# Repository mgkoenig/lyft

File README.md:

# LYFT
LYFT is a sophisticated remote control for the famous IKEA BEKANT desk. It replaces the original controller and adds a number of useful features for more options and convenience. 

Check [tindie](https://www.tindie.com/products/mgkoenig/lyft/) to see a fully assembled version of LYFT in action. 

If you would like to read a featured article about LYFT you can find some on [ikeahackers](https://ikeahackers.net/2024/03/ikea-adjustable-desk.html) or [hackaday](https://hackaday.com/2024/04/18/lyft-standing-up-for-better-ikea-bekant-control/) respectively. 

## Features 
#### Saving Desk Positions  
The controller can store up to four different desk positions. These positions are easily accessable using the four memory buttons.

#### Display 
The controller is equipped with a 3-digit 7-segment display which allows you to read the current desk height either in centimeters or inch. Furthermore, you can adjust the display brigtness as well as the display-on time. If the shown desk height is not accurate you can adjust the value using the 'level correction' feature by plus/minus 9 centimeters. 
  
#### Audio Signals  
In order to give some acoustic feedback the controller has a build-in audio transducer. The volume of the audio signals can be set in the settings menu but also be disabled.
  
#### Automatic Driving Mode
One of the most useful features is the automatic driving mode which allows you to move the desk to a saved position without holding a button all the time. 

#### Safety Pin 
On the basis of the original controller LYFT also supports a safety pin. The pin is needed to move the desk and to unlock the settings menu for changes. It is fully compatible with the original IKEA safety pin which is provided with the BEKANT desk. 

Further details and how to use these features are described in the [manual](/manual.pdf).

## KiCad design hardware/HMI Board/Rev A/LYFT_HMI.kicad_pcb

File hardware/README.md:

# LYFT Hardware 
The LYFT hardware consists of two PCB boards. A controller board and an HMI board. 

### Controller Board
The controller board holds the SAM-D21 micrcontroller and handles all the motor control as well as the HMI communication. Desk motors are addressed using the LIN bus while the HMI board is connected via I2C. A buzzer is used to generate sounds and alarms. 

### HMI Board
The HMI board is equipped with an AS1115 display driver to control both the 7-segment display and all six buttons. 

### Library
Parts which are not existent in the standard KiCad library are published here.

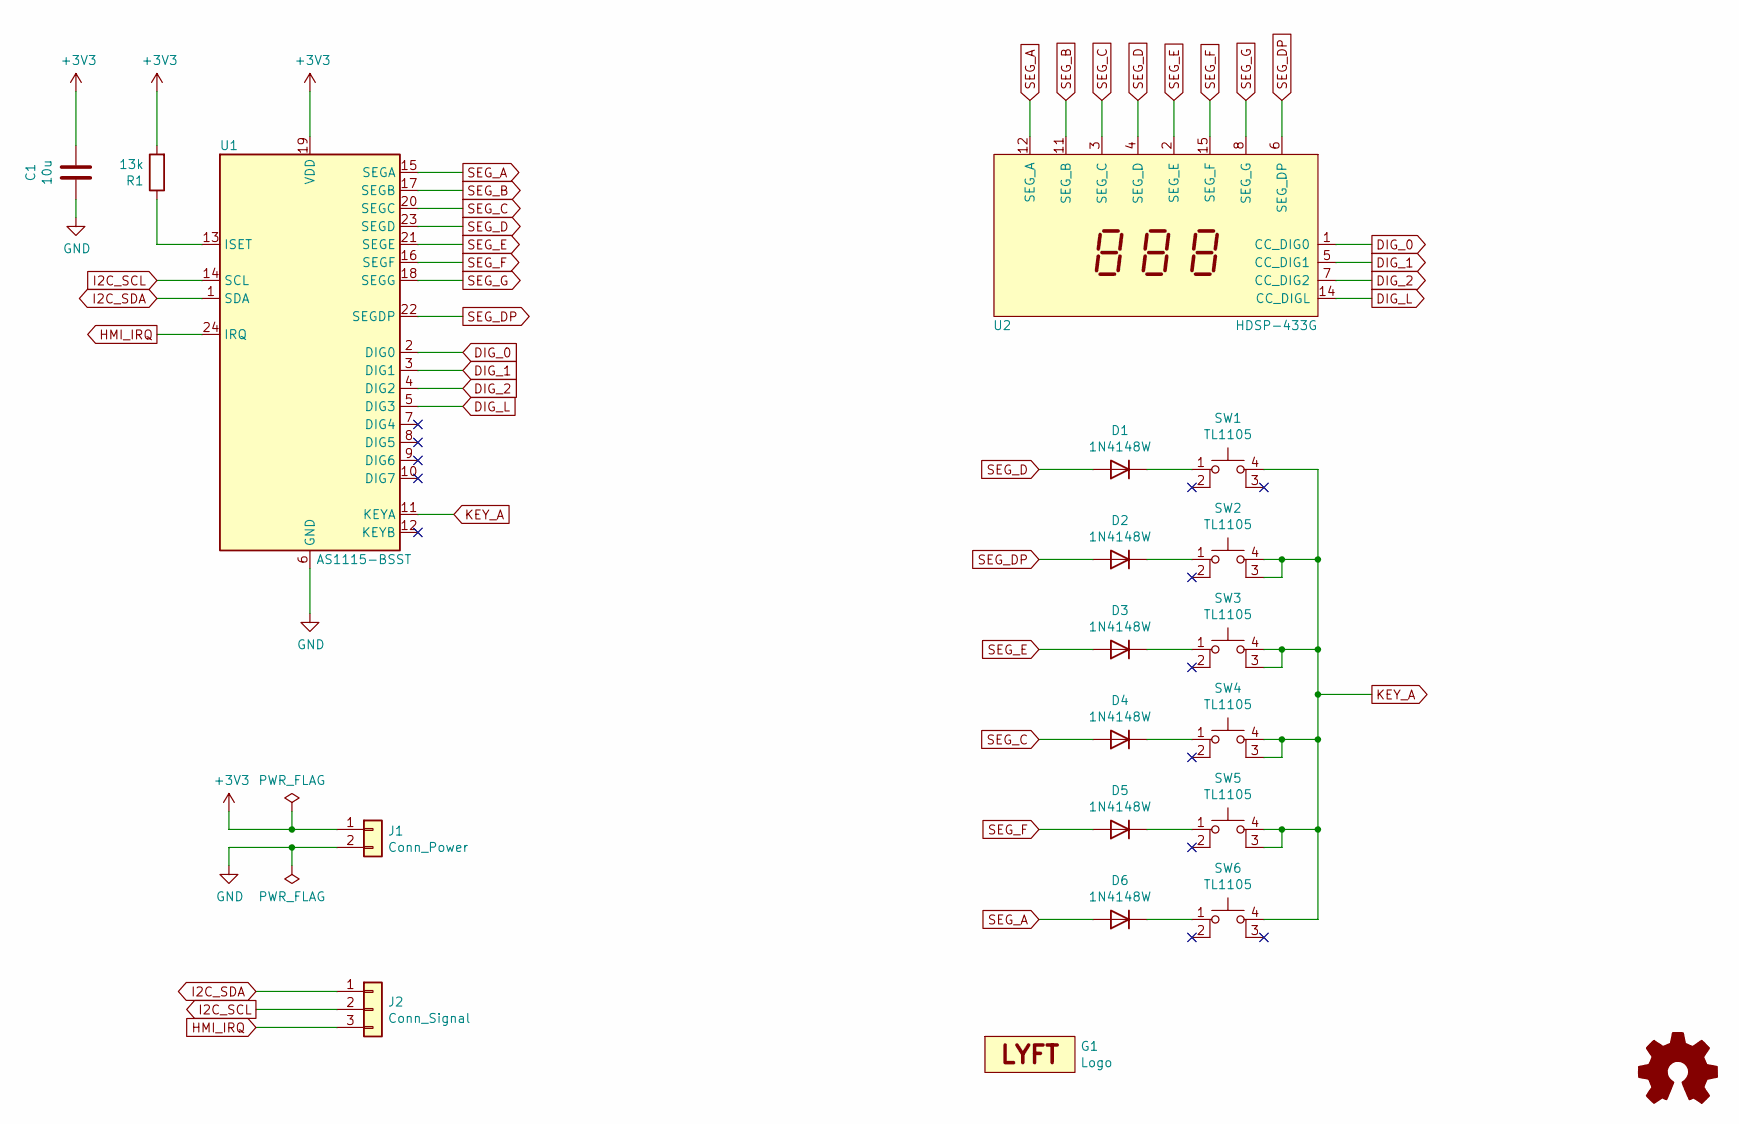
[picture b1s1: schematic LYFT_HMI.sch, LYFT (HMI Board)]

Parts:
C1: 10u; C_0805_2012Metric_Pad1.18x1.45mm_HandSolder
D1, D2, D3, D4, D5, D6: 1N4148W; D_SOD-123
G1: Logo; LYFT-Logo_10x4
J1: Conn_Power; PinSocket_1x02_P2.54mm_Vertical
J2: Conn_Signal; PinSocket_1x03_P2.54mm_Vertical
R1: 13k; R_0805_2012Metric_Pad1.20x1.40mm_HandSolder
SW1, SW2, SW3, SW4, SW5, SW6: TL1105; SW_TH_Tactile_Omron_B3F-10xx_Center
U1: AS1115-BSST; QSOP-24_3.9x8.7mm_P0.635mm
U2: HDSP-433G; HDSP-433

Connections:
+3V3: C1.1, J1.1, R1.2, U1.19 (VDD)
DIG_0: U1.2 (DIG0), U2.1 (CC_DIG0)
DIG_1: U1.3 (DIG1), U2.5 (CC_DIG1)
DIG_2: U1.4 (DIG2), U2.7 (CC_DIG2)
DIG_L: U1.5 (DIG3), U2.14 (CC_DIGL)
GND: C1.2, J1.2, U1.6 (GND)
HMI_IRQ: J2.3, U1.24 (IRQ)
I2C_SCL: J2.2, U1.14 (SCL)
I2C_SDA: J2.1, U1.1 (SDA)
KEY_A: SW1.4 (A), SW2.3 (K), SW2.4 (A), SW3.3 (K), SW3.4 (A), SW4.3 (K), SW4.4 (A), SW5.3 (K), SW5.4 (A), SW6.4 (A), U1.11 (KEYA)
unnamed: D1.1 (K), SW1.1
unnamed: D2.1 (K), SW2.1
unnamed: D3.1 (K), SW3.1
unnamed: D4.1 (K), SW4.1
unnamed: D5.1 (K), SW5.1
unnamed: D6.1 (K), SW6.1
unnamed: R1.1, U1.13 (ISET)
SEG_A: D6.2 (A), U1.15 (SEGA), U2.12 (SEG_A)
SEG_B: U1.17 (SEGB), U2.11 (SEG_B)
SEG_C: D4.2 (A), U1.20 (SEGC), U2.3 (SEG_C)
SEG_D: D1.2 (A), U1.23 (SEGD), U2.4 (SEG_D)
SEG_DP: D2.2 (A), U1.22 (SEGDP), U2.6 (SEG_DP)
SEG_E: D3.2 (A), U1.21 (SEGE), U2.2 (SEG_E)
SEG_F: D5.2 (A), U1.16 (SEGF), U2.15 (SEG_F)
SEG_G: U1.18 (SEGG), U2.8 (SEG_G)

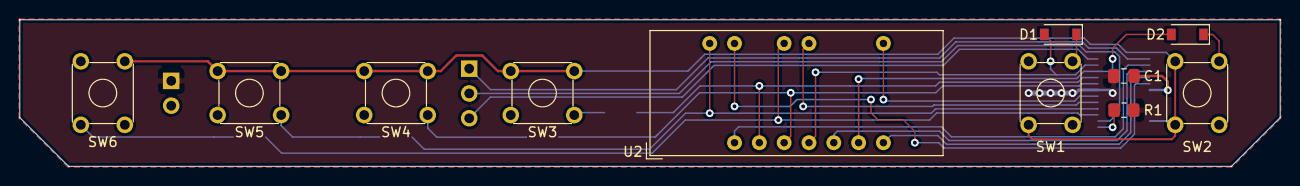
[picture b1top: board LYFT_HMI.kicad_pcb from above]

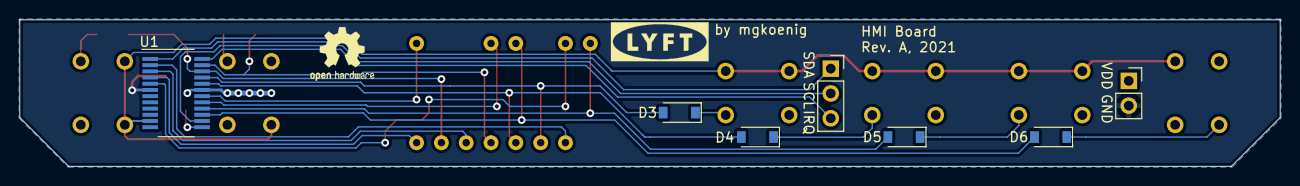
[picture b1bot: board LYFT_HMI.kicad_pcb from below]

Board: 2 copper layers, 129.0 x 15.0 mm, 19 parts (8 on the bottom side), 25 nets.

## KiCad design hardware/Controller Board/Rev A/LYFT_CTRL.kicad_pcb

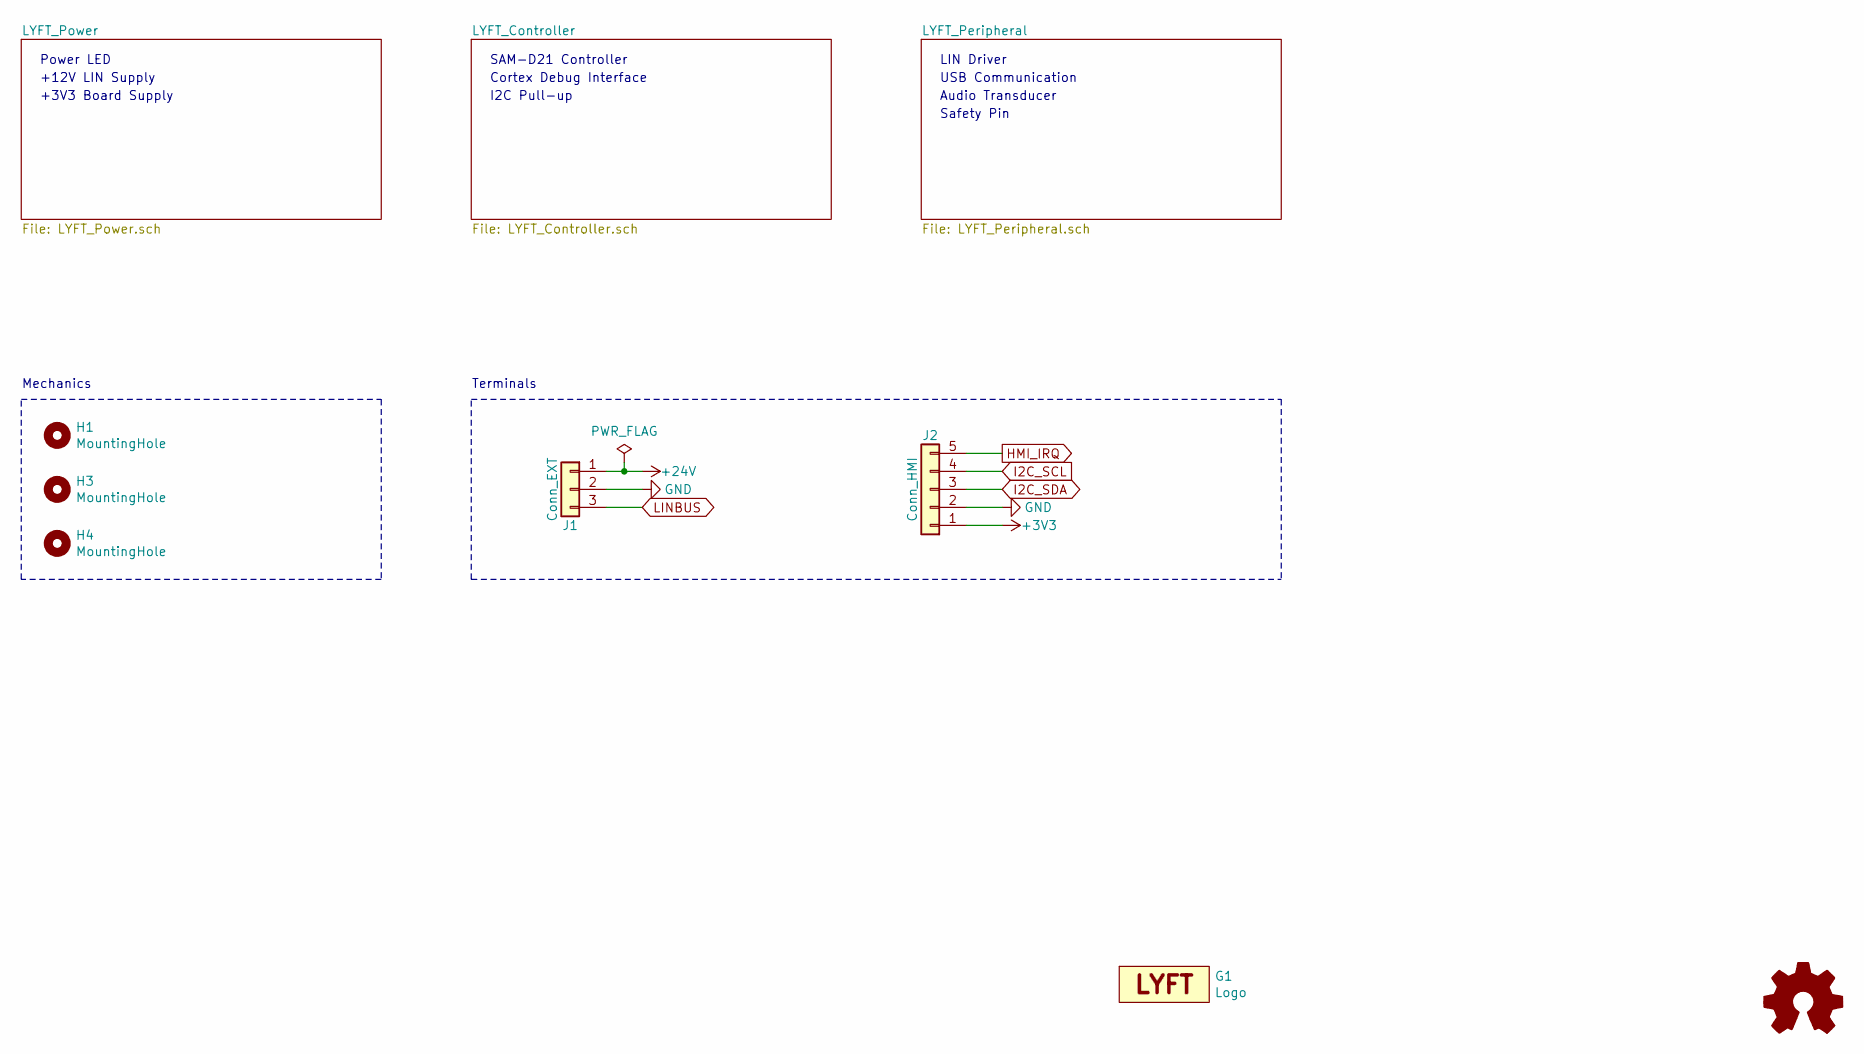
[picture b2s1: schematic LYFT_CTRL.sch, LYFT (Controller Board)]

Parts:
G1: Logo; LYFT-Logo_10x4
H1, H3, H4: MountingHole; MountingHole_3.2mm_M3
J1: Conn_EXT; PinHeader_1x03_P2.54mm_Vertical
J2: Conn_HMI; PinHeader_1x05_P2.54mm_Vertical

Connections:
+3V3: J2.1; also elsewhere on the board
+24V: J1.1; also elsewhere on the board
GND: J1.2, J2.2; also elsewhere on the board
HMI_IRQ: J2.5; also elsewhere on the board
I2C_SCL: J2.4; also elsewhere on the board
I2C_SDA: J2.3; also elsewhere on the board
LINBUS: J1.3; also elsewhere on the board

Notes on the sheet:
Mechanics
+3V3 Board Supply
SAM-D21 Controller
Cortex Debug Interface
I2C Pull-up
LIN Driver
USB Communication
Audio Transducer
Terminals
+12V LIN Supply
Safety Pin
Power LED

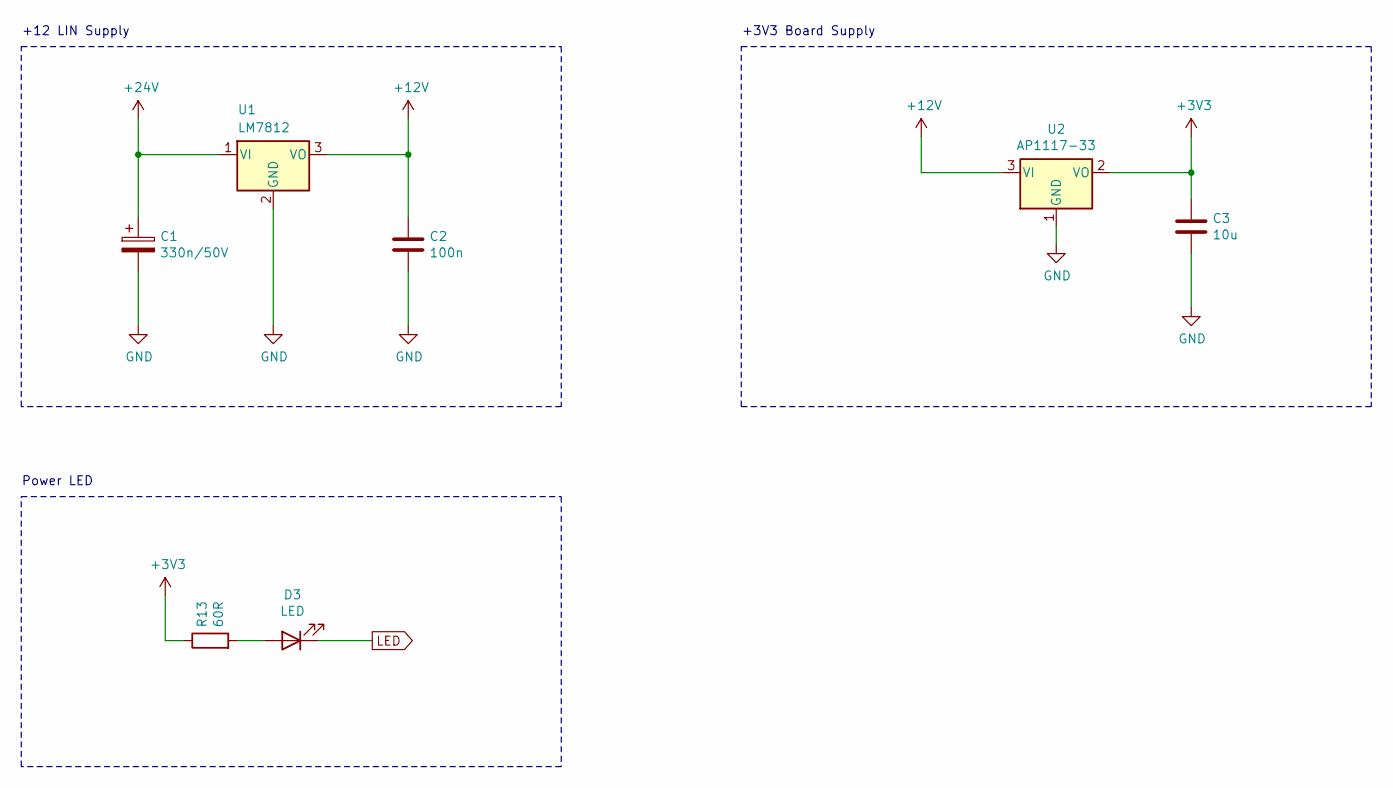
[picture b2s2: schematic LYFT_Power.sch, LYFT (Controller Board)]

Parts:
C1: 330n/50V; CP_Elec_4x5.4
C2: 100n; C_0805_2012Metric_Pad1.18x1.45mm_HandSolder
C3: 10u; C_0805_2012Metric_Pad1.18x1.45mm_HandSolder
D3: LED; LED_0805_2012Metric_Pad1.15x1.40mm_HandSolder
R13: 60R; R_0805_2012Metric_Pad1.20x1.40mm_HandSolder
U1: LM7812; TO-263-3_TabPin2
U2: AP1117-33; SOT-223-3_TabPin2

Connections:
+3V3: C3.1, R13.1, U2.2 (VO); also elsewhere on the board
+12V: C2.1, U1.3 (VO), U2.3 (VI); also elsewhere on the board
+24V: C1.1, U1.1 (VI); also elsewhere on the board
GND: C1.2, C2.2, C3.2, U1.2 (GND), U2.1 (GND); also elsewhere on the board
LED: D3.1 (K); also elsewhere on the board
unnamed: D3.2 (A), R13.2

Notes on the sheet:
+12 LIN Supply
+3V3 Board Supply
Power LED

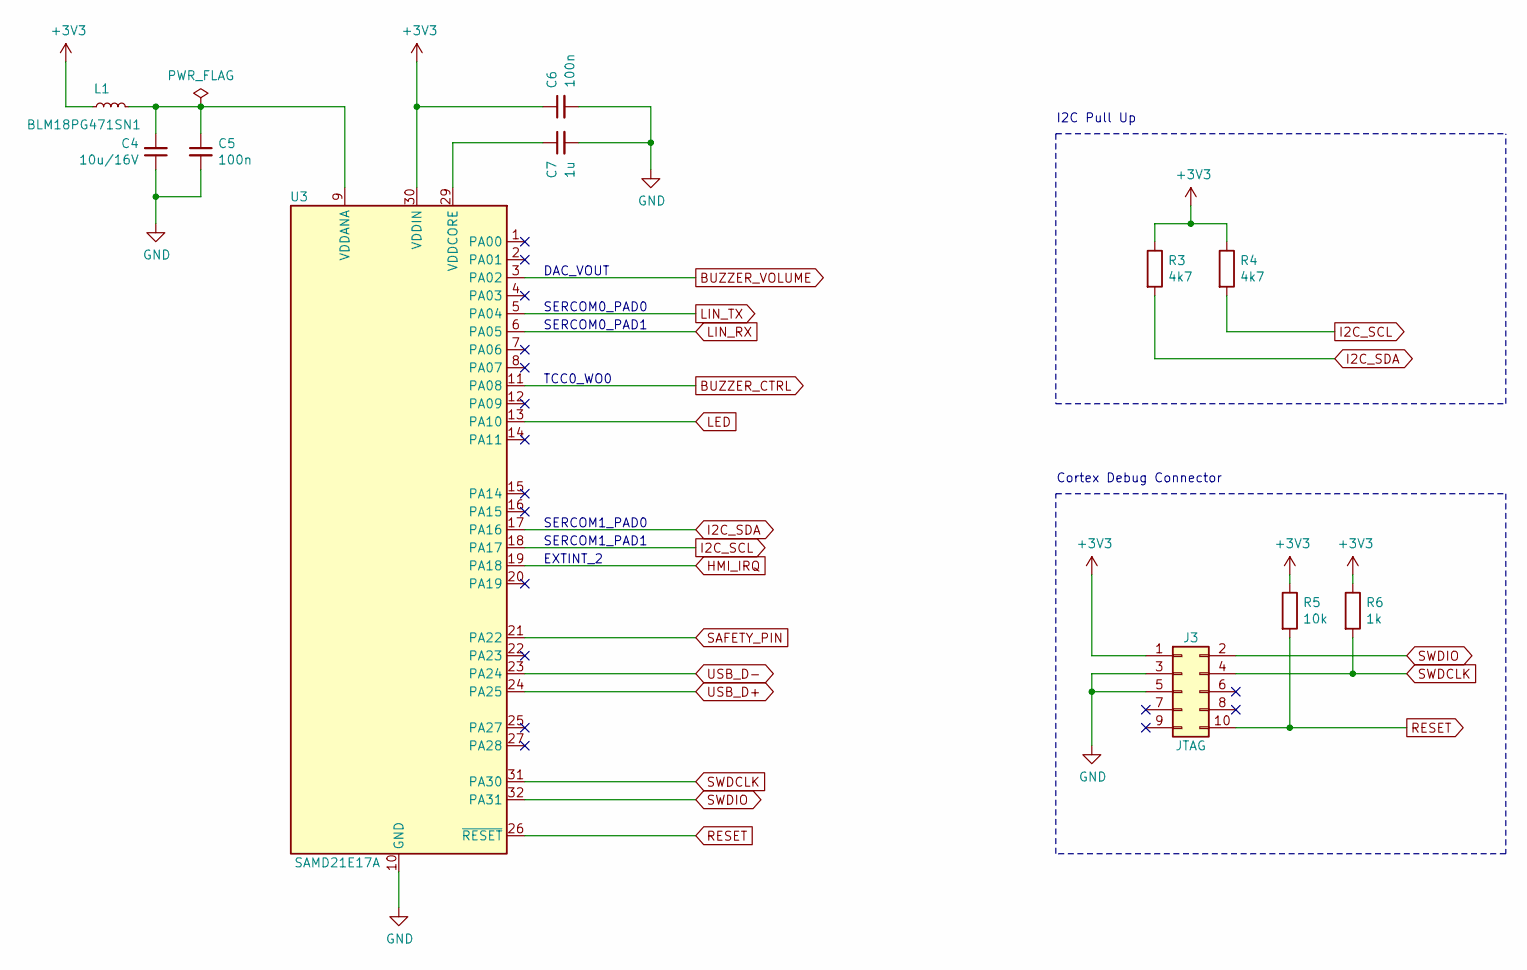
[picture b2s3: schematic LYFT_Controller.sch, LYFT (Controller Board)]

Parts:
C4: 10u/16V; C_0805_2012Metric_Pad1.18x1.45mm_HandSolder
C5, C6: 100n; C_0805_2012Metric_Pad1.18x1.45mm_HandSolder
C7: 1u; C_0805_2012Metric_Pad1.18x1.45mm_HandSolder
J3: JTAG; PinHeader_2x05_P1.27mm_Vertical
L1: BLM18PG471SN1; L_0805_2012Metric_Pad1.15x1.40mm_HandSolder
R3, R4: 4k7; R_0805_2012Metric_Pad1.20x1.40mm_HandSolder
R5: 10k; R_0805_2012Metric_Pad1.20x1.40mm_HandSolder
R6: 1k; R_0805_2012Metric_Pad1.20x1.40mm_HandSolder
U3: SAMD21E17A; TQFP-32_7x7mm_P0.8mm

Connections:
+3V3: C6.1, J3.1, L1.2, R3.1, R4.1, R5.1, R6.1, U3.30 (VDDIN); also elsewhere on the board
BUZZER_CTRL: U3.11 (PA08); also elsewhere on the board
BUZZER_VOLUME: U3.3 (PA02); also elsewhere on the board
GND: C4.1, C5.2, C6.2, C7.2, J3.3, J3.5, U3.10 (GND), U3.28 (GND); also elsewhere on the board
HMI_IRQ: U3.19 (PA18); also elsewhere on the board
I2C_SCL: R4.2, U3.18 (PA17); also elsewhere on the board
I2C_SDA: R3.2, U3.17 (PA16); also elsewhere on the board
LED: U3.13 (PA10); also elsewhere on the board
LIN_RX: U3.6 (PA05); also elsewhere on the board
LIN_TX: U3.5 (PA04); also elsewhere on the board
unnamed: C4.2, C5.1, L1.1, U3.9 (VDDANA)
unnamed: C7.1, U3.29 (VDDCORE)
RESET: J3.10, R5.2, U3.26 (~RESET)
SAFETY_PIN: U3.21 (PA22); also elsewhere on the board
SWDCLK: J3.4, R6.2, U3.31 (PA30)
SWDIO: J3.2, U3.32 (PA31)
USB_D+: U3.24 (PA25); also elsewhere on the board
USB_D-: U3.23 (PA24); also elsewhere on the board

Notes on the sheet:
Cortex Debug Connector
I2C Pull Up
TCC0_WO0
EXTINT_2
SERCOM0_PAD0
SERCOM0_PAD1
SERCOM1_PAD0
SERCOM1_PAD1
DAC_VOUT

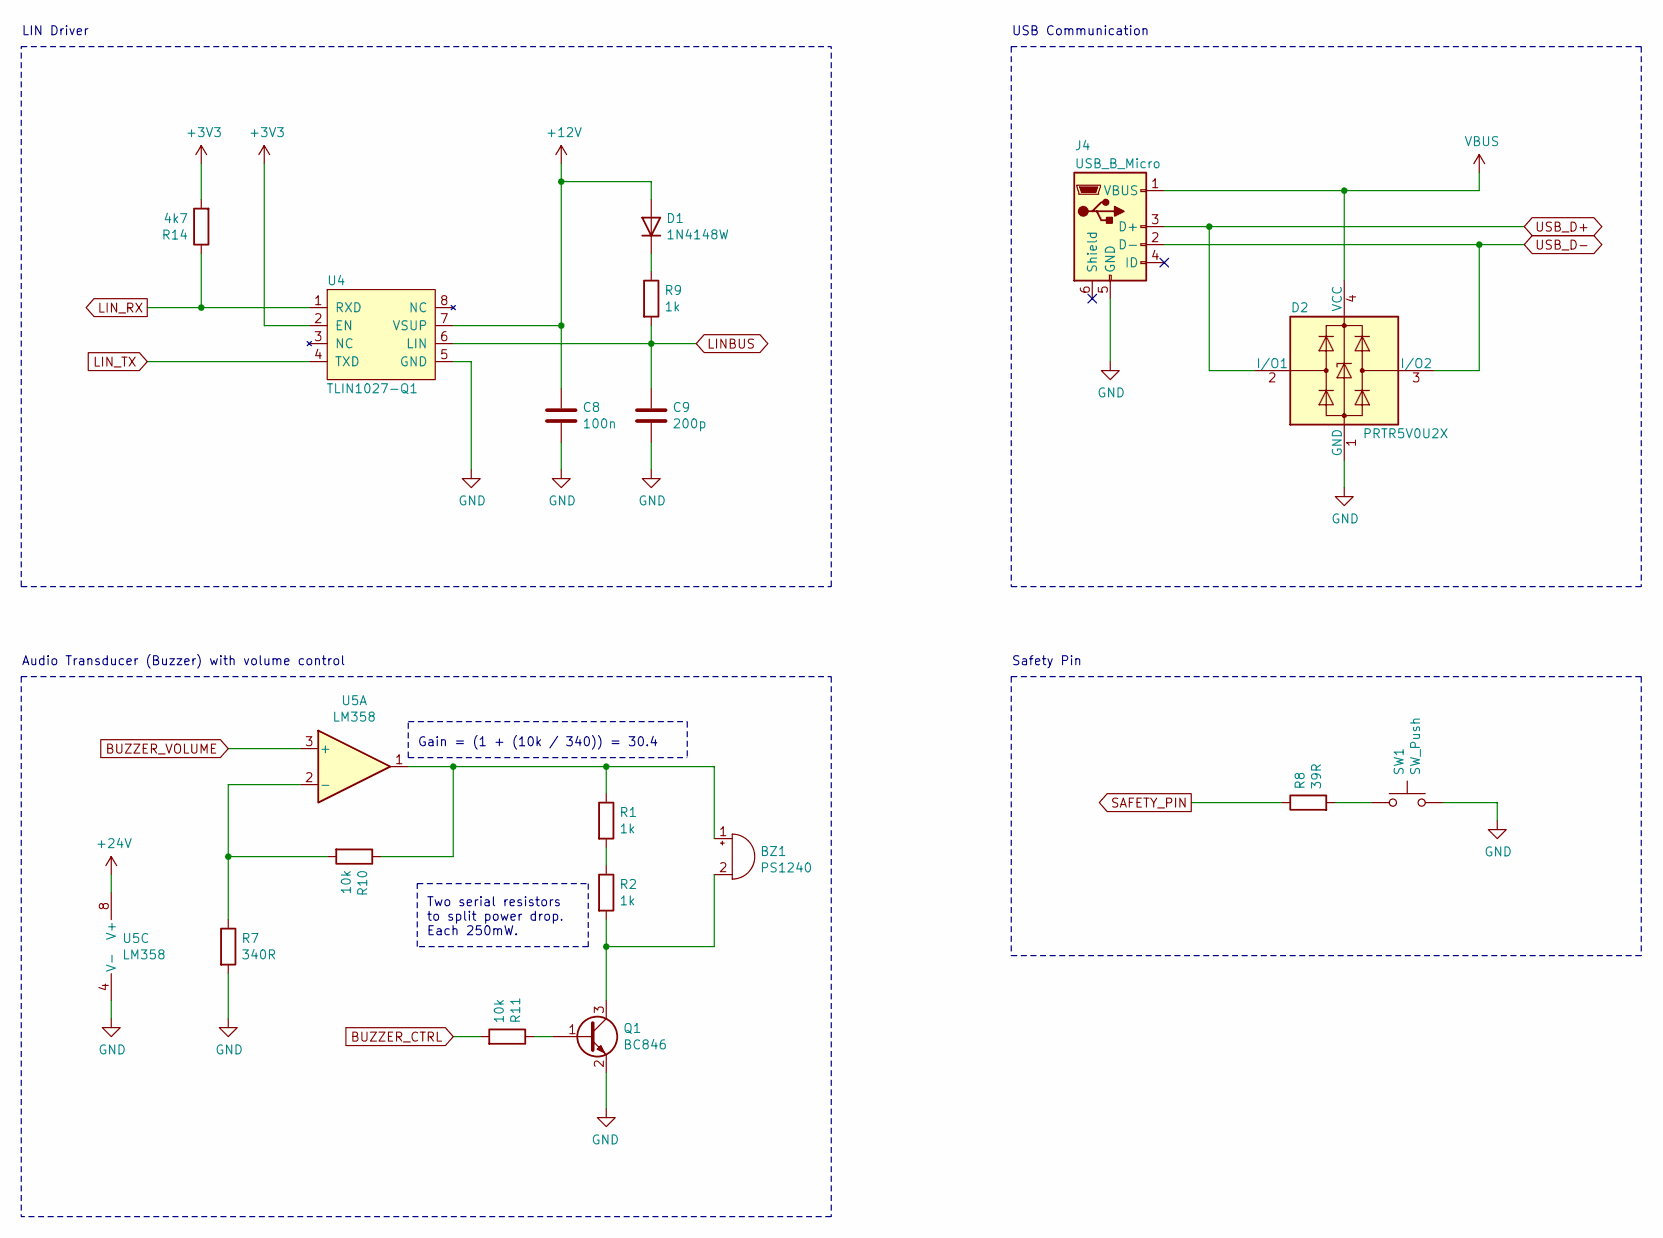
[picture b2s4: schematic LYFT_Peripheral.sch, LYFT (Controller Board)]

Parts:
BZ1: PS1240; Buzzer_TDK_PS1240P02BT_D12.2mm_H6.5mm
C8: 100n; C_0805_2012Metric_Pad1.18x1.45mm_HandSolder
C9: 200p; C_0805_2012Metric_Pad1.18x1.45mm_HandSolder
D1: 1N4148W; D_SOD-123
D2: PRTR5V0U2X; SOT-143
J4: USB_B_Micro; USB_Micro-B_Wuerth_614105150721_Vertical_CircularHoles
Q1: BC846; SOT-23
R1, R2, R9: 1k; R_0805_2012Metric_Pad1.20x1.40mm_HandSolder
R7: 340R; R_0805_2012Metric_Pad1.20x1.40mm_HandSolder
R8: 39R; R_0805_2012Metric_Pad1.20x1.40mm_HandSolder
R10, R11: 10k; R_0805_2012Metric_Pad1.20x1.40mm_HandSolder
R14: 4k7; R_0805_2012Metric_Pad1.20x1.40mm_HandSolder
SW1: SW_Push; SW_Tactile_SPST_Angled_PTS645Vx31-2LFS
U4: TLIN1027-Q1; SOIC-8_3.9x4.9mm_P1.27mm
U5: LM358; SO-8_3.9x4.9mm_P1.27mm

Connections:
+3V3: R14.2, U4.2 (EN); also elsewhere on the board
+12V: C8.2, D1.2 (A), U4.7 (VSUP); also elsewhere on the board
+24V: U5.8 (V+); also elsewhere on the board
BUZZER_CTRL: R11.2; also elsewhere on the board
BUZZER_VOLUME: U5.3 (+); also elsewhere on the board
GND: C8.1, C9.1, D2.1 (GND), J4.5 (GND), Q1.2 (E), R7.2, SW1.2, U4.5 (GND), U5.4 (V-); also elsewhere on the board
LINBUS: C9.2, R9.2, U4.6 (LIN); also elsewhere on the board
LIN_RX: R14.1, U4.1 (RXD); also elsewhere on the board
LIN_TX: U4.4 (TXD); also elsewhere on the board
unnamed: BZ1.1 (-), R1.1, R10.1, U5.1
unnamed: BZ1.2 (+), Q1.3 (C), R2.2
unnamed: D1.1 (K), R9.1
unnamed: Q1.1 (B), R11.1
unnamed: R1.2, R2.1
unnamed: R8.2, SW1.1
unnamed: R7.1, R10.2, U5.2 (-)
SAFETY_PIN: R8.1; also elsewhere on the board
USB_D+: D2.2 (I/O1), J4.3 (D+); also elsewhere on the board
USB_D-: D2.3 (I/O2), J4.2 (D-); also elsewhere on the board
VBUS: D2.4 (VCC), J4.1 (VBUS)

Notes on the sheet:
USB Communication
LIN Driver
Safety Pin
Audio Transducer (Buzzer) with volume control
Two serial resistors to split power drop. Each 250mW.
Gain = (1 + (10k / 340)) = 30.4

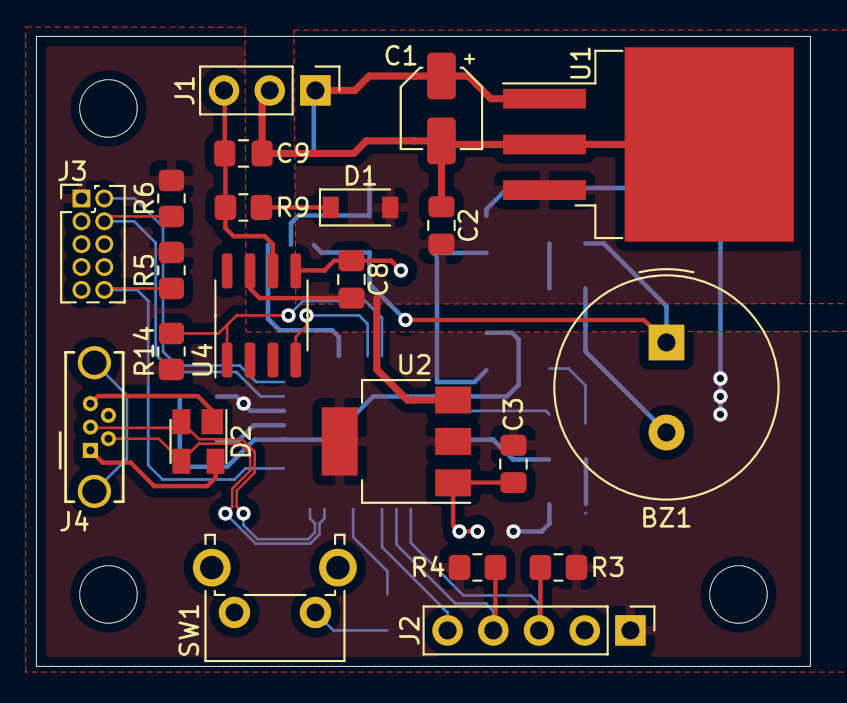
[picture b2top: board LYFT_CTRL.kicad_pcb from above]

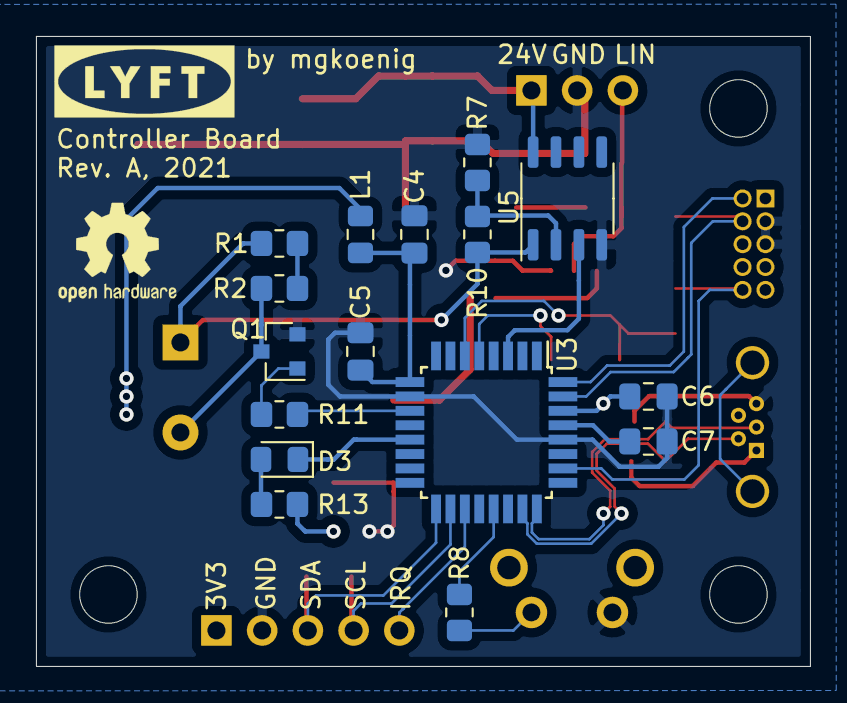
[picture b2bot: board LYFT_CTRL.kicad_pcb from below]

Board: 2 copper layers, 43.0 x 35.0 mm, 42 parts (17 on the bottom side), 30 nets.

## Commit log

2021-12-27 obsolete file
2021-12-27 Updated latest schematic file
2021-12-27 created changelog
2021-12-29 updated description
2021-12-30 architecture illustration
2021-12-30 more detailed firmware description
2022-01-22 modified license
    Changed from MIT to GNU GPL license.
2022-02-12 v1.0.1
2022-02-12 v1.0.1
    Improved behaviour if no safety pin is plugged-in while display is on.
2022-02-13 added "button map"
2022-02-17 added documentation
2022-02-22 corrected comment typo
2022-02-22 added documentation
    Removed #defines of current SW version since they are nowhere used.
2022-02-22 updated changelog
2022-02-26 [feature] automatic drive mode
    - New feature: automatic drive mode
    - Code improvements: utility function to compute difference as absolute value, screen behaviour on start-up without safety pin)
    - Code optimizations (unified button actions to common functions)
    - Adjusted motor controls (min/max values and safety margin)
    - Further documentations
2022-02-26 [feature] automatic drive mode
    Added NVM entry (for the configuration file) to store the new value of the drive mode (automatic or hand driven)
2024-02-21 Update README.md
    more detailed description
2024-04-08 added manual.pdf
2024-04-08 added manual
    manual compatible with firmware version 1.1.0
2024-04-08 added design model
2024-04-09 delete doc directory
    files moved to other place
2024-04-09 add manual and model
2025-02-07 Fix typo in manual.pdf
    Fixed Typo on page 7 Desk Moving Mode:
    From "automatic mode is more comfartable."
    To "automatic mode is more comfartable."
2025-10-09 Add files via upload
    complete project folder to run with microchip studio (containing all sources, settings and project files)
